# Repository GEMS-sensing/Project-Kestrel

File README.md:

<!--  -->

# Project-Kestrel
Core board for a Flight data logger, featuring interfaces to Talon boards ([SDI-12 Talon](https://github.com/GEMS-sensing/Talon-SDI12), [I2C Talon](https://github.com/GEMS-sensing/Talon-I2C), [Auxiliary Talon](https://github.com/GEMS-sensing/Talon-Auxiliary)) and external battery board ([Gonk](https://github.com/GEMS-sensing/Project-Gonk)). This is the core component of [Flight data logger](https://github.com/GEMS-sensing/DFM_-_Flight?tab=readme-ov-file).

# Repo Roadmap
#### [Documents](Documentation/) 

General document and image storage for repo and README

#### [Hardware](Hardware/)

Current board files (Eagle), Bill of Materials (BoM), and other design documents

#### [Production](Production/)

Contains the various Gerber and pick and place files required to have the Printed Circuit Boards (PCBs) manufactured or populated 

#### [Software](Software/)

The software associated with the piece of hardware, this is usually diagnostic software used for verifying or investigating the hardware

<!-- #### [Mechanical](Mechanical/)

Mechanical design files and assembly documents -->

<!-- #### [Testing](Testing/)

Scripts and results from the testing process and development process. Contains more detailed information about documented issues among other testing. 
 -->

## Overview
* **Type:** Logger
* **Interfaces:** Talon, Gonk
* **Release Version:** v1.9 - 2023/06/23

<!--  -->

## Features
### On-Board
* Modular interfaces for Talon daughterboards (x4)
	* Isolated I2C interface
	* Individual power control and monitoring
	* Firmware selectable GPIO/UART interface
	* Polarized connector
* Battery board interface 
	* I2C interface for battery power reporting
	* Polarized connector
* Multi-charger input
	* Solar panel (6V) input
	* High power (>2A) input for fast charge in no solar situations
* [Particle BSoM](https://docs.particle.io/b-series/) M.2 interface
	* Interface for the highly flexible Particle BSoM module
* Micro USB interface 
	* Programming and charging
* Power switch
	* Complete disconnect 
	* Tri position to allow for 'ON'-'TESTING'-'OFF' modes
* LED status indicators 
* Non-Contact safe mode circuit 
	* Safe mode circuit controlled by Hall effect sensor to allow for triggering with magnet from outside logger box
* Multi-rail power system
	* Allow for independent control of subsystems, on-board and off-board
* On-board GPS Module with battery backup for improved hot start
* SD Card interface
* On-board sensing for self diagnostics
	* Voltage/current sensing (8 positions)
	* Temperature
	* Humidity
	* Accelerometer, 3 axis
	* Magnatometer, 3 axis
	* Ambient light, multi channel
* Interchangeable SIM card (future support)
* RTC with rechargeable battery backup
* FRAM storage for low power backhaul batching
* Long period WatchDog control to prevent critical lockups 

<!-- ### Interface
* I<sup>2</sup>C
* M12 circular connector  -->

<!-- <picture>
  <source media="(prefers-color-scheme: dark)" srcset="Documents/Pinout_LIGHT.png">
  
</picture> -->

<!-- ## Specifications
* **Voltage - Supply:** 3.3V
* **Voltage - Logic:** 3.3V
* **Input Current (Avg, 1s period): 30.95&mu;A @ 3.3V**
* **Input Current (Avg, 5s period): 107.43&mu;A @ 3.3V**
* **Input Current (Max): 0.45mA @ 3.3V**

#### Sensor
**Temperature** [^1]
* Range: -40 ~ 125°C 
* Accuracy: &plusmn; 0.2°C
* Repeatability: &plusmn; 0.04°C

**Pressure** [^2]
* Range: 300 ~ 1200 hPa  
* Accuracy: &plusmn; 1 hPa
* Repeatability: &plusmn; 0.06 hPa

**Humidity** [^1]
* Range: 0 ~ 100%
* Accuracy: &plusmn; 2%
* Repeatability: 0.08%

[^1]: [SHT31 Datasheet](https://sensirion.com/media/documents/213E6A3B/63A5A569/Datasheet_SHT3x_DIS.pdf)
[^2]: [DPS368 Datasheet](https://www.infineon.com/dgdl/Infineon-DPS368-DS-v01_00-EN.pdf?fileId=5546d46269e1c019016a0c45105d4b40) -->

<!-- ## Version History

`v0.0` - Initial primal version with screw terminal

`v0.1` - Initial 'hard mount' version, using M12 connector

`v1.0` - Removed pullup select[^3], added logic level buffer and voltage reg on input

`v1.1` - Moved via away from connector pads to prevent bridging when soldering 

`v2.0` - Fixed issue with address select jumper[^3] -->

<!-- ## Jumper Settings 

> [!IMPORTANT]
> Jumper settings valid for version `v2.0` and beyond[^3]

[^3]: See Errata

**Configuration Jumpers**
| Jumper | Purpose | Open | Closed | Default | 
| ------ | ------- | ---------- | ---------- | ----- | 
| `JP1` | I<sup>2</sup>C Address Select | Base Address<sup>&dagger;</sup> | Alt Address<sup>&Dagger;</sup> | Open |

&dagger; SHT31 = `0x44`, DPS368 = `0x76`

&Dagger; SHT31 = `0x44`, DPS368 = `0x77`

 -->

## Version History

v1.7 updates:
- Connected DONE line on U26 to ensure consistent trip (prevent factory reset while using hall effect control)
- Changed label for 'STAT' led in upper right corner to 'SYS', this was done to reflect the current usage of the indicator and to eliminate confusion between this indicator and the indicator lamp for the battery charge (also labeled 'STAT')
- Switched amber LEDs to yellow

## Known Issues/Errata

#### Solder Jumper Stencil

**Version Affected:** All

**Issue:** Solar input does not support very low impedance sources (e.g. lead acid battery) - see details in issue [#20](https://github.com/GEMS-sensing/Project-Kestrel/issues/20)

**Workaround:** 

* Avoid use of low impedance batteries for input
* Include series impedance to prevent current spikes (not desirable)
* Perform board patch described in issue [#20](https://github.com/GEMS-sensing/Project-Kestrel/issues/20)

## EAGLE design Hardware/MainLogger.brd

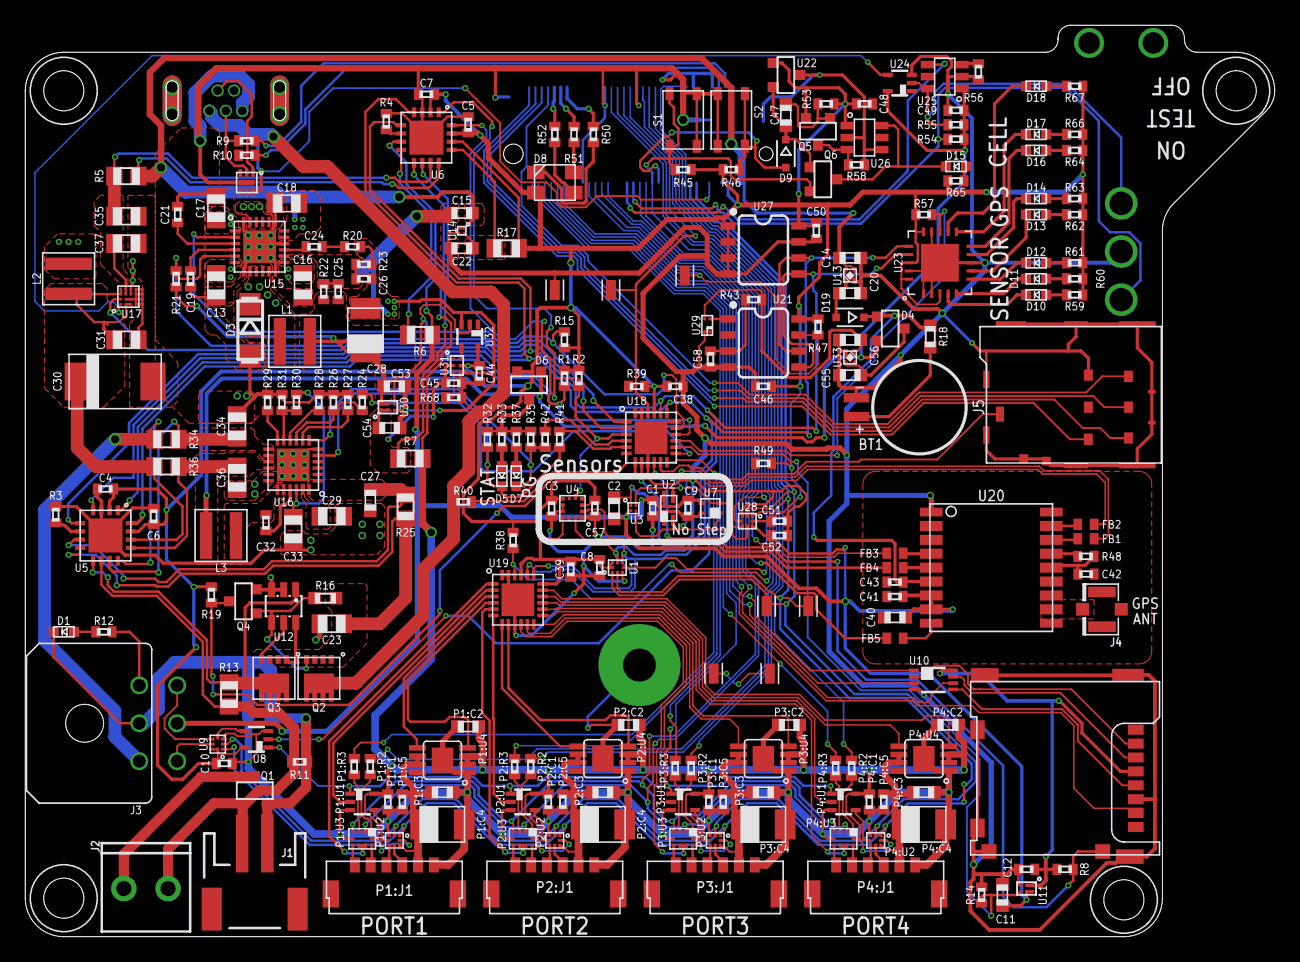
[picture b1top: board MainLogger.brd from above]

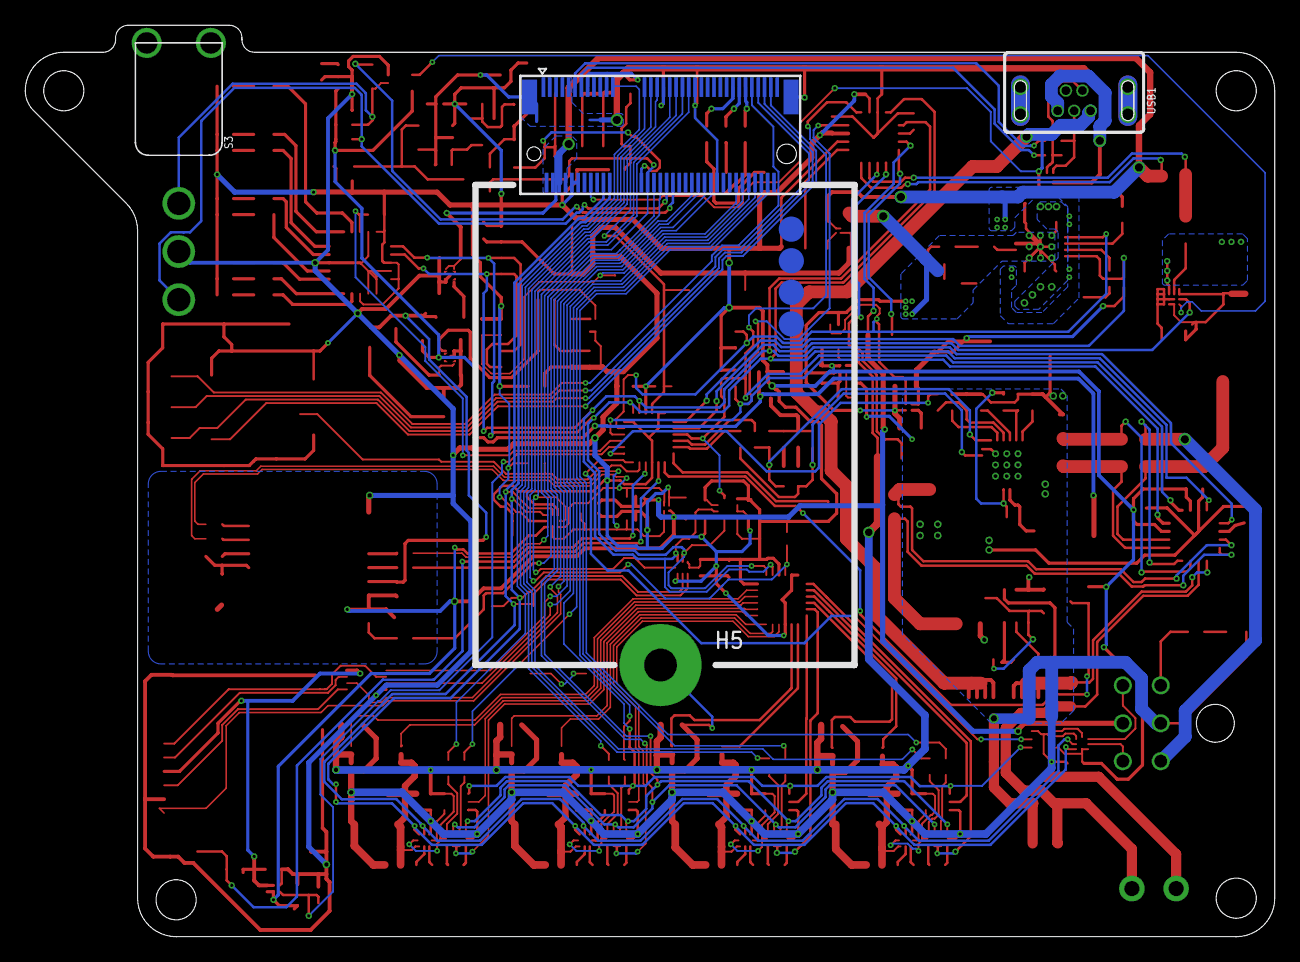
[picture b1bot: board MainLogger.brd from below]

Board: 2 copper layers, 98.9 x 72.1 mm, 262 parts (3 on the bottom side), 202 nets.

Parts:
$3_190_$_2021-12-10_02-09-55: B_SERIES_M.2EKEY_3042; PARTICLE_M.2EKEY
BT1: BATTERY_COINML621; ML621S
C1, C3, C4, C5, C6, C7, C8, C9, C10, C12, C38, C39, C41, C43, C44, C45, C46, C48, C49, C50, C51, C52, C57: 0.1uF; C0402
C2: 2.2uF; C0603
C11, C14, C15, C20, C22, C27, C40, C47, C53, C54, C55, C56: 1uF; C0603
C13, C16, C17, C18, C34: 22uF; C0805
C19: 1nF; C0402
C21, C25: 10nF; C0402
C23, C29, C35, C36, C37: 10uF; C0805
C24: 39pF; C0402
C26, C58: 100pF; C0402
C28: 100uF; C1411_TANT
C30: 220uF; C2917
C31: 1.5uF; C0805
C32: 47nF; C0402
C33: 4.7uF; C0805
C42: 47pF; C0402
D1, D12, D18: LEDRED0603; LED_0603
D2: RCLAMP3654; DFN_6_1.6X1.6
D3: CDBA3100; DO214AC
D4: BAT54C; SOT23-3
D5, D10, D13, D15, D16: LEDGREEN0603; LED_0603
D6: SOT23-3
D7, D11, D14, D17: LEDYELLOW0603; LED_0603
D8: CLVBA-FKA
D9, D19: BAT54WS; SOD323-R
FB1, FB2, FB3, FB4, FB5: R0402
H1, H2, H3, H4: 4_40
J1: JST-2-SMD
J2: SCREWTERMINAL-3.5MM-2_ROUND_RESTRICT
J3: GEMS_POWER_PLUGINPUT_RT; 2X3_MICROFIT_RT
J4: U.FL
J5: SIM_CDNANO_SF72; SIM_SF72
L1, L3: 1uH; WE-MAIA(4.1X4.1)
L2: 0.47uH; WE-MAPI(4.1X4.1)
P1:C1, P1:C5, P2:C1, P2:C5, P3:C1, P3:C5, P4:C1, P4:C5: 0.1uF; C0402
P1:C2, P2:C2, P3:C2, P4:C2: 2.2uF; C0603
P1:C3, P2:C3, P3:C3, P4:C3: 1uF; C0603
P1:C4, P2:C4, P3:C4, P4:C4: 100uF; C1411_TANT
P1:J1, P2:J1, P3:J1, P4:J1: CONN_TALON_LOGGER; 1X06_MICROLOCKPLUS_RT
P1:R2, P1:R3, P2:R2, P2:R3, P3:R2, P3:R3, P4:R2, P4:R3: 1k; R0402
P1:U1, P2:U1, P3:U1, P4:U1: SN74AUP1G08DCK; DCK_R-PDSO-G5
P1:U2, P2:U2, P3:U2, P4:U2: FXMAR2102UMLP; UQFN-8_1.4X1.2
P1:U3, P2:U3, P3:U3, P4:U3: FSA2258; MICROPAK_10
P1:U4, P2:U4, P3:U4, P4:U4: AP2411; MSOP_8EP
Q1, Q4: DMG3404; SOT23-3
Q2, Q3: MOSFET_PCH-DMP3036SFG; POWERDI3333-8
Q5, Q6: NX2301P; SOT23-3
R1, R2, R11, R19, R26, R32, R35, R40, R41, R42, R54, R55: 1M; R0402
R3, R20: 20k; R0402
R4: 2k; R0402
R5, R13, R25, R34, R36: 2m; R0805
R6, R7, R17: 10m; R0805
R8, R14, R15, R21, R30, R31, R38, R39, R47, R49, R53, R57: 100k; R0402
R9, R10: 27R; R0402
R12, R43: 1k; R0402
R16: 470k; R0603
R18: 750R; R0603
R22, R29, R33, R45, R46, R65: 10k; R0402
R23, R37: 2.7k; R0402
R24: 0R; R0402
R27, R28, R59, R60, R61, R62, R63, R64, R66, R67: 220R; R0402
R48: 10; R0402
R50, R51, R52, R68: 5.6k; R0402
R56: 130k; R0402
R58: 11k; R0402
S1, S2: BUTTON4.2X3.2; SWITCH_4.2X3.2
S3: SPDT7103K2CWAV2; 7103K2CWAV2
SD1: MICROSDMOLEX_503182; MICROSD_MOLEX_5031821852
TP1, TP2, TP5, TP6, TP7, TP8, TP9: TESTPOINT_DNP_RCU; TESTPOINT_0603
U1, U9, U28: FXMAR2102UMLP; UQFN-8_1.4X1.2
U2: VEML3328; VEML6075
U3: MMC5633; BGA_4
U4: BMA456; LGA-12_2X2
U5, U6: PAC1934QFN; QFN16
U7: SHT40; SHT4X
U8: SN74AUP1G08DCK; DCK_R-PDSO-G5
U10: SN74AUP3G34DCU; DCU_(R-PDSO-G8)
U11, U30: TCK111G; WCSP_6
U12: LTC4412S6; SOT23-6L
U13: TPS7A0331PDQ; X2SON
U14: LP59073.3VYKE; YKE0004
U15: MIC22602; QFN24_POWER
U16: BQ25616; QFN24_POWER
U17: TPS61282D; YFP0016
U18, U19: PCAL9535AQFN; QFN24
U20: MAX-M8W; MAX-M8
U21: MCP79412SOIC; SO08
U22: HALL_EFFECT_SI7201; SOT23-3
U23: PCA9634QFN; QFN20_5X5
U24: SN74LVC1G17DCK; DCK_R-PDSO-G5
U25, U26: TPL5010DDC; DDC_R-PDSO-G6
U27: MB85RC; SO08
U29: SIT1552; LD-4
U31: FPF2195BUCX; WCSP_6
U32: DCK_R-PDSO-G5
U33: TPS7A0218PDQ; X2SON
USB1: USB_MICROMUSB-K152; MUSB-K152-30

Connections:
3V3_AUX: C1.1, C2.1, C9.1, C11.1, C40.1, C41.1, C52.1, J3.5, R6.1, U2.4, U3.B1, U6.7, U7.3, U11.A2, U11.B2, U20.7, U20.8, U28.8
3V3_AUX_EN: R15.1, U15.2, U18.17, U30.C2, U32.2
3V3_AUX_PG: R21.1, U15.5, U18.1
3V3_BULK+: C25.1, C28.ANODE, C53.1, L1.P$2, R6.2, R21.2, R22.2, U6.8, U30.A2, U30.B2
3V3_CORE: $3_190_$_2021-12-10_02-09-55.10, $3_190_$_2021-12-10_02-09-55.12, C3.1, C4.1, C5.1, C6.1, C7.1, C8.1, C10.1, C38.1, C39.1, C44.1, C46.1, C48.1, C50.1, C51.1, C57.1, D6.2, D8.2, Q5.2, R1.2, R2.2, R15.2, R17.2, R19.2, R38.2, R39.2, R45.2, R46.2, R47.2, R49.2, R53.2, R57.2, R59.2, R60.2, R61.2, R62.2, R63.2, R64.2, R65.2, R66.2, R67.2, U1.1, U1.8, U4.3, U4.7, U4.10, U5.2, U5.15, U6.2, U6.14, U6.15, U8.5, U9.1, U9.8, U18.21, U19.18, U19.21, U21.8, U22.1, U23.3, U23.15, U23.18, U23.20, U26.1, U27.8, U28.1, U31.B2, U32.5
3V3_CORE+: C22.1, R17.1, U6.13, U14.A2
3V3_SD: C12.1, R8.2, SD1.4, U10.8, U11.A1, U11.B1
3V3_SD_EN: R14.2, U11.C2, U18.14
3V3_TALON: P1:C1.1, P1:C2.1, P1:U1.5, P1:U2.1, P1:U3.10, P1:U4.2, P1:U4.3, P2:C1.1, P2:C2.1, P2:U1.5, P2:U2.1, P2:U3.10, P2:U4.2, P2:U4.3, P3:C1.1, P3:C2.1, P3:U1.5, P3:U2.1, P3:U3.10, P3:U4.2, P3:U4.3, P4:C1.1, P4:C2.1, P4:U1.5, P4:U2.1, P4:U3.10, P4:U4.2, P4:U4.3, R7.2, U6.9
3V3_TALON+: C45.1, C54.1, R7.1, U6.10, U30.A1, U30.B1, U31.B1
!CE: R24.1, U18.13
!CHG_PG: D7.CATHODE, R35.1, R42.2, U16.7
!MODE: $3_190_$_2021-12-10_02-09-55.32, D9.A, R46.1, S2.1, S2.2
!RESET: $3_190_$_2021-12-10_02-09-55.34, FB5.2, Q6.2, R45.1, S1.1, S1.2
!TALON1_FAULT: P1:U4.5, U19.3
!TALON2_FAULT: P2:U4.5, U19.7
!TALON3_FAULT: P3:U4.5, U19.12
!TALON4_FAULT: P4:U4.5, U19.16
BAT: J3.1, R34.2, U5.12
BAT_CHG: C34.1, R34.1, U5.11, U16.13, U16.14
BCKP_GPS: C43.1, D4.1, D19.C, R18.1, U20.6
BCKP_GPS_REG: C20.1, D19.A, U13.1
BCKP_PRIME: C55.1, D4.3, U33.3, U33.4
BCKP_RTC: C58.1, R43.2, U21.3
BTST: C32.2, U16.21
CHG_SOURCE: Q4.3, R19.1, U18.7
CHG_STAT: D5.CATHODE, R32.1, R41.2, U16.5
CLK_OSC: U21.1, U29.2
COMP: C24.1, U15.15
CSA_EN: R1.1, U5.16, U6.16, U18.16
D+: $3_190_$_2021-12-10_02-09-55.11, R9.1
D+_IN: D2.2, R9.2, USB1.3
D-: $3_190_$_2021-12-10_02-09-55.13, R10.1
D-_IN: D2.1, R10.2, USB1.2
DELAY: C21.1, U15.3
EN_MAIN: U17.A1, U24.4
EN_MAIN_OD: R55.2, S3.1, U24.2, U25.6
FAULT_BUS: D1.ANODE, R12.2
FB: C25.2, C26.1, R22.1, R23.2, U15.14
GND: $3_190_$_2021-12-10_02-09-55.1, $3_190_$_2021-12-10_02-09-55.3, $3_190_$_2021-12-10_02-09-55.5, $3_190_$_2021-12-10_02-09-55.7, $3_190_$_2021-12-10_02-09-55.9, $3_190_$_2021-12-10_02-09-55.15, $3_190_$_2021-12-10_02-09-55.21, $3_190_$_2021-12-10_02-09-55.39, $3_190_$_2021-12-10_02-09-55.49, $3_190_$_2021-12-10_02-09-55.56, $3_190_$_2021-12-10_02-09-55.76, $3_190_$_2021-12-10_02-09-55.77, $3_190_$_2021-12-10_02-09-55.GND, BT1.-, C1.2, C2.2, C3.2, C4.2, C5.2, C6.2, C7.2, C8.2, C9.2, C10.2, C11.2, C12.2, C13.2, C14.2, C15.2, C16.2, C17.2, C18.2, C19.2, C20.2, C21.2, C22.2, C23.2, C26.2, C27.2, C28.CATHODE, C29.2, C30.-, C31.2, C33.2, C34.2, C35.2, C36.2, C37.2, C38.2, C39.2, C40.2, C41.2, C42.2, C43.2, C44.2, C45.2, C46.2, C48.2, C49.2, C50.2, C51.2, C52.2, C53.2, C54.2, C55.2, C56.2, C57.2, C58.2, D1.CATHODE, D2.EP, D3.A, J1.1, J3.2, J4.1, J4.2, J5.5, J5.CSW, J5.GND@1, J5.GND@2, J5.GND@3, J5.GND@4, J5.GND@5, J5.GND@6, J5.GND@7, J5.GND@8, J5.GND@9, J5.GND@10, P1:C1.2, P1:C2.2, P1:C3.2, P1:C4.CATHODE, P1:C5.2, P1:J1.1, P1:U1.3, P1:U2.4, P1:U3.5, P1:U4.1, P1:U4.EP, P2:C1.2, P2:C2.2, P2:C3.2, P2:C4.CATHODE, P2:C5.2, P2:J1.1, P2:U1.3, P2:U2.4, P2:U3.5, P2:U4.1, P2:U4.EP, P3:C1.2, P3:C2.2, P3:C3.2, P3:C4.CATHODE, P3:C5.2, P3:J1.1, P3:U1.3, P3:U2.4, P3:U3.5, P3:U4.1, P3:U4.EP, P4:C1.2, P4:C2.2, P4:C3.2, P4:C4.CATHODE, P4:C5.2, P4:J1.1, P4:U1.3, P4:U2.4, P4:U3.5, P4:U4.1, P4:U4.EP, Q1.2, Q4.2, R3.1, R4.1, R11.1, R14.1, R20.1, R23.1, R26.1, R27.1, R28.1, R29.2, R31.1, R56.1, R58.1, R68.1, S1.3, S1.4, S2.3, S2.4, S3.2, SD1.6, SD1.BODY@1, SD1.BODY@2, SD1.BODY@3, SD1.BODY@4, SD1.BODY@5, SD1.SW1, TP1.1, U1.4, U2.1, U3.A1, U4.1, U4.8, U4.9, U5.3, U5.EP, U6.3, U6.EP, U7.4, U8.3, U9.4, U10.4, U11.C1, U12.2, U12.3, U13.2, U13.EP, U14.B2, U15.7, U15.12, U15.16, U15.19, U15.24, U15.EP, U15.EP@1, U15.EP@2, U15.EP@3, U15.EP@4, U15.EP@5, U15.EP@6, U15.EP@7, U15.EP@8, U15.EP@9, U16.6, U16.17, U16.18, U16.EP, U16.EP@1, U16.EP@2, U16.EP@3, U16.EP@4, U16.EP@5, U16.EP@6, U16.EP@7, U16.EP@8, U16.EP@9, U17.B2, U17.C2, U17.D1, U17.D2, U17.D3, U17.D4, U18.9, U18.18, U18.23, U18.24, U18.EP, U19.9, U19.23, U19.24, U19.EP, U20.1, U20.10, U20.12, U21.4, U22.3, U23.1, U23.2, U23.8, U23.14, U23.19, U23.EP, U24.3, U25.2, U26.2, U26.4, U27.1, U27.2, U27.3, U27.4, U27.7, U28.4, U29.1, U29.4, U30.C1, U31.C2, U32.3, U33.2, U33.EP, USB1.5
GPS_ANT: J4.FEED, U20.11
GPS_INT: FB4.1, U18.8
GPS_INT_CLEAN: FB4.2, U20.5
I2C_EXT_EN: U8.2, U18.12
I2C_EXT_EN_OUT: U8.4, U9.5
I2C_GLOBAL_EN: $3_190_$_2021-12-10_02-09-55.64, P1:U1.1, P2:U1.1, P3:U1.1, P4:U1.1, U8.1
I2C_OB_EN: $3_190_$_2021-12-10_02-09-55.45, U1.5, U28.5
ICHG: R28.2, U16.10
ILIM: R27.2, U16.8
LED_BLUE: $3_190_$_2021-12-10_02-09-55.65, R52.2
LED_EN: R57.1, U18.15, U23.13
LED_GREEN: $3_190_$_2021-12-10_02-09-55.63, R51.2
LED_RED: $3_190_$_2021-12-10_02-09-55.61, R50.2
MISO: $3_190_$_2021-12-10_02-09-55.50, SD1.7
MOSI: $3_190_$_2021-12-10_02-09-55.52, U10.1
MOSI_BUF: SD1.3, U10.7
unnamed: R3.2, U5.6
unnamed: Q3.4, U12.5
unnamed: R41.1, U18.5
unnamed: BT1.+, R18.2
unnamed: R40.1, U18.6
unnamed: R42.1, U18.4
unnamed: R24.2, R26.2, U16.9
unnamed: C47.1, D9.C, Q6.1, U22.2
unnamed: D15.CATHODE, Q6.3, U26.6
unnamed: C47.2, Q5.1, R53.1
unnamed: D15.ANODE, R65.1
unnamed: R4.2, U6.6
unnamed: D7.ANODE, R37.1
unnamed: R68.2, U31.C1
unnamed: D5.ANODE, R33.1
unnamed: D8.3, R52.1
unnamed: D8.4, R51.1
unnamed: D8.1, R50.1
unnamed: FB5.1, U20.9
unnamed: J3.3, R12.1
unnamed: U31.A2, U32.4
unnamed: R56.2, U25.3
unnamed: Q5.3, R58.2, U26.3
unnamed: C24.2, R20.2
unnamed: D10.CATHODE, U23.4
unnamed: D11.CATHODE, U23.5
unnamed: D12.CATHODE, U23.6
unnamed: D13.CATHODE, U23.7
unnamed: D14.CATHODE, U23.9
unnamed: D16.CATHODE, U23.10
unnamed: D17.CATHODE, U23.11
unnamed: D18.CATHODE, U23.12
unnamed: D10.ANODE, R59.1
unnamed: D11.ANODE, R60.1
unnamed: D12.ANODE, R61.1
unnamed: D13.ANODE, R62.1
unnamed: D14.ANODE, R63.1
unnamed: D16.ANODE, R64.1
unnamed: D17.ANODE, R66.1
unnamed: D18.ANODE, R67.1
OB_INT: $3_190_$_2021-12-10_02-09-55.43, R39.1, TP7.1, U18.22
P1:3V3_TALON: P1:C3.1, P1:C4.ANODE, P1:C5.1, P1:J1.2, P1:U2.8, P1:U4.6, P1:U4.7
P1:I2C_EN_LOCAL: P1:U1.4, P1:U2.5
P1:N$1: P1:R2.1, P1:U3.1
P1:N$2: P1:R3.1, P1:U3.3
P1:RX_TALON: P1:J1.6, P1:U3.6
P1:SCL_EXT: P1:J1.4, P1:U2.6
P1:SDA_EXT: P1:J1.3, P1:U2.7
P1:TX_TALON: P1:J1.5, P1:U3.9
P2:3V3_TALON: P2:C3.1, P2:C4.ANODE, P2:C5.1, P2:J1.2, P2:U2.8, P2:U4.6, P2:U4.7
P2:I2C_EN_LOCAL: P2:U1.4, P2:U2.5
P2:N$1: P2:R2.1, P2:U3.1
P2:N$2: P2:R3.1, P2:U3.3
P2:RX_TALON: P2:J1.6, P2:U3.6
P2:SCL_EXT: P2:J1.4, P2:U2.6
P2:SDA_EXT: P2:J1.3, P2:U2.7
P2:TX_TALON: P2:J1.5, P2:U3.9
P3:3V3_TALON: P3:C3.1, P3:C4.ANODE, P3:C5.1, P3:J1.2, P3:U2.8, P3:U4.6, P3:U4.7
P3:I2C_EN_LOCAL: P3:U1.4, P3:U2.5
P3:N$1: P3:R2.1, P3:U3.1
P3:N$2: P3:R3.1, P3:U3.3
P3:RX_TALON: P3:J1.6, P3:U3.6
P3:SCL_EXT: P3:J1.4, P3:U2.6
P3:SDA_EXT: P3:J1.3, P3:U2.7
P3:TX_TALON: P3:J1.5, P3:U3.9
P4:3V3_TALON: P4:C3.1, P4:C4.ANODE, P4:C5.1, P4:J1.2, P4:U2.8, P4:U4.6, P4:U4.7
P4:I2C_EN_LOCAL: P4:U1.4, P4:U2.5
P4:N$1: P4:R2.1, P4:U3.1
P4:N$2: P4:R3.1, P4:U3.3
P4:RX_TALON: P4:J1.6, P4:U3.6
P4:SCL_EXT: P4:J1.4, P4:U2.6
P4:SDA_EXT: P4:J1.3, P4:U2.7
P4:TX_TALON: P4:J1.5, P4:U3.9
PMID: C29.1, U16.23
RC: C19.1, U15.4
REGN: C33.1, R30.2, U16.22
RTC_INT: $3_190_$_2021-12-10_02-09-55.62, R47.1, TP2.1, U21.7
RX: $3_190_$_2021-12-10_02-09-55.38, P1:U3.4, P2:U3.4, P3:U3.4, P4:U3.4, TP9.1
SCK: $3_190_$_2021-12-10_02-09-55.54, U10.3
SCK_BUF: SD1.5, U10.5
SCL: $3_190_$_2021-12-10_02-09-55.20, P1:U2.3, P2:U2.3, P3:U2.3, P4:U2.3, TP6.1, U1.2, U9.3, U28.3
SCL_AUX: FB2.1, U2.3, U3.A2, U7.2, U28.6
SCL_EXT: J3.6, U9.6
SCL_GPS: FB2.2, U20.17
SCL_OB: U1.7, U4.12, U5.4, U6.4, U18.19, U19.19, U21.6, U23.16, U27.6
SDA: $3_190_$_2021-12-10_02-09-55.22, P1:U2.2, P2:U2.2, P3:U2.2, P4:U2.2, TP5.1, U1.3, U9.2, U28.2
SDA_AUX: FB1.1, U2.2, U3.B2, U7.1, U28.7
SDA_EXT: J3.4, U9.7
SDA_GPS: FB1.2, U20.16
SDA_OB: U1.6, U4.2, U5.5, U6.5, U18.20, U19.20, U21.5, U23.17, U27.5
SD_CD: R8.1, SD1.SW2, U18.10
SD_CS: $3_190_$_2021-12-10_02-09-55.48, U10.6
SD_CS_BUF: SD1.2, U10.2
SENSOR_INT: R2.1, U4.5, U5.1, U6.1, U18.3
SIM_CD: J5.DSW, R49.1, U18.11
SIM_CLK: $3_190_$_2021-12-10_02-09-55.71, J5.3
SIM_DATA: $3_190_$_2021-12-10_02-09-55.73, J5.7
SIM_RST: $3_190_$_2021-12-10_02-09-55.69, J5.2
SIM_VCC: $3_190_$_2021-12-10_02-09-55.67, J5.1
SOLAR+: J1.2, J2.1, Q1.1, R11.2, R13.1, U5.10
SOLAR-: J2.2, Q1.3
STAT_CORE: D6.3, R32.2, R33.2, R35.2, R37.2
ST_CORE: Q2.4, Q4.1, R16.1, U12.4
SW: C32.1, L3.P$1, U16.19, U16.20
SW1: D3.C, L1.P$1, U15.8, U15.9, U15.10, U15.11, U15.20, U15.21, U15.22, U15.23
SW2: L2.P$2, U17.C3, U17.C4
SYS: C30.+, C31.1, L2.P$1, R36.2, U5.14, U17.A3, U17.A4, U17.B1, U17.C1
SYSCORE: C36.1, C49.1, D4.2, D6.1, L3.P$2, R36.1, R54.1, R55.1, U5.13, U16.15, U16.16, U24.5, U25.1
TALON1_EN: P1:U4.4, U19.4
TALON1_GPIOA: $3_190_$_2021-12-10_02-09-55.37, P1:R2.2
TALON1_GPIOB: $3_190_$_2021-12-10_02-09-55.72, P1:R3.2
TALON1_I2C_EN: P1:U1.2, U19.2
TALON1_SEL: P1:U3.7, P1:U3.8, U19.1
TALON2_EN: P2:U4.4, U19.8
TALON2_GPIOA: $3_190_$_2021-12-10_02-09-55.35, P2:R2.2
TALON2_GPIOB: $3_190_$_2021-12-10_02-09-55.70, P2:R3.2
TALON2_I2C_EN: P2:U1.2, U19.6
TALON2_SEL: P2:U3.7, P2:U3.8, U19.5
TALON3_EN: P3:U4.4, U19.13
TALON3_GPIOA: $3_190_$_2021-12-10_02-09-55.33, P3:R2.2
TALON3_GPIOB: $3_190_$_2021-12-10_02-09-55.68, P3:R3.2
TALON3_I2C_EN: P3:U1.2, U19.11
TALON3_SEL: P3:U3.7, P3:U3.8, U19.10
TALON4_EN: P4:U4.4, U19.17
TALON4_GPIOA: $3_190_$_2021-12-10_02-09-55.23, P4:R2.2
TALON4_GPIOB: $3_190_$_2021-12-10_02-09-55.66, P4:R3.2
TALON4_I2C_EN: P4:U1.2, U19.15
TALON4_SEL: P4:U3.7, P4:U3.8, U19.14
TALON_INT: $3_190_$_2021-12-10_02-09-55.41, R38.1, U19.22
TEST: $3_190_$_2021-12-10_02-09-55.40, R54.2, S3.3
TIMEPULSE: $3_190_$_2021-12-10_02-09-55.47, FB3.1
TIMEPULSE_CLEAN: FB3.2, U20.4
TS: R30.1, R31.2, U16.11
TX: $3_190_$_2021-12-10_02-09-55.36, P1:U3.2, P2:U3.2, P3:U3.2, P4:U3.2, TP8.1
VBULK: $3_190_$_2021-12-10_02-09-55.2, $3_190_$_2021-12-10_02-09-55.4, $3_190_$_2021-12-10_02-09-55.6, $3_190_$_2021-12-10_02-09-55.8, C13.1, C14.1, C15.1, C16.1, C17.1, C18.1, R5.1, U6.12, U13.3, U13.4, U14.A1, U14.B1, U15.1, U15.6, U15.13, U15.17, U15.18
VBULK+: C35.1, C37.1, R5.2, U6.11, U17.B3, U17.B4
VBULK_PG: U17.A2, U18.2
VBUS: C27.1, R25.2, U5.7, U16.1, U16.24
VCC_RF: C42.1, R48.1, U20.14
VDD_CLK: C56.1, R43.1, U29.3, U33.1
VPRIME: C23.1, Q2.1, Q2.2, Q2.3, Q3.1, Q3.2, Q3.3, R16.2, R25.1, U5.8, U12.6
VSET: R29.1, U16.12
VSOLAR: Q3.EP@1, Q3.EP@2, Q3.EP@3, Q3.EP@4, Q3.EP@5, R13.2, U5.9, U12.1
VUSB: $3_190_$_2021-12-10_02-09-55.16, D2.6, Q2.EP@1, Q2.EP@2, Q2.EP@3, Q2.EP@4, Q2.EP@5, R40.2, USB1.1
V_ANT: R48.2, U20.15
WDT_DONE: $3_190_$_2021-12-10_02-09-55.42, U25.4

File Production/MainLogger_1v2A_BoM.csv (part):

"Qty","Value","Device","Package","Parts","Description","DIGIKEY","DISP","MF","MPN","PROD_ID","SF_ID","VALUE","VALUE_PART",
"1","","CONN_02-JST-2MM-SMT","JST-2-SMD","J1","Genaric 2 terminal header","455-1749-1-ND","","JST","S2B-PH-SM4-TB(LF)(SN)","CONN-11443","","","",
"1","","CONN_023.5MM_ROUND_RESTRICT","SCREWTERMINAL-3.5MM-2_ROUND_RESTRICT","J2","Genaric 2 terminal header","ED2635-ND","","On Shore","OSTTE020161","","","","",
"1","","DIODE_CCBAT54CSOT23","SOT23-3","D6","Dual Diode, Common Cathode","BAT54CLT1GOSCT-ND","","ON Semiconductor","BAT54CLT1G","","","","",
"5","","FERRITE_BEAD1KS0402","R0402","FB1, FB2, FB3, FB4, FB5","Genaric Ferrite Bead","490-4003-1-ND","","Murata","BLM15HD102SN1D","","","","",
"4","","MOUNTING_HOLE4_NP","4_40","H1, H2, H3, H4","Genaric Mechanical Mounting Hole","DNP","","N/A","DNP","","","","",
"29","0.1uF","C-EU0.1UFC0402","C0402","C1, C4, C5, C6, C7, C8, C9, C10, C12, C14, C20, C38, C39, C41, C43, C46, C48, C49, C50, C51, C52, P1:C1, P1:C5, P2:C1, P2:C5, P3:C1, P3:C5, P4:C1, P4:C5","CAPACITOR, European symbol","490-4759-1-ND","","Murata","GCM155R71C104KA55D","","","","",
"1","0.47uH","INDUCTOR_MAPI_4.1X4.1","WE-MAPI(4.1X4.1)","L2","Genaric Inductor","732-744383560047HTCT-ND","","Wurth","744383560047HT","","","","",
"3","0R","R-EU_0.0R0402","R0402","R3, R4, R24","RESISTOR, European symbol","311-0.0JRCT-ND","","Yageo","RC0402JR-070RL","","","","0",
"1","1.5uF","C-EU1.5UFC0805","C0805","C31","CAPACITOR, European symbol","399-4930-1-ND","","Kemet","C0805C155K4RACTU","","","","",
"1","10","R-EU_10R0402","R0402","R48","RESISTOR, European symbol","A129603CT-ND","","TE","CRGCQ0402F10R","","","","10",
"15","100k","R-EU_100KR0402","R0402","P1:R1, P2:R1, P3:R1, P4:R1, R8, R14, R15, R21, R30, R31, R47, R49, R53, R56, R57","RESISTOR, European symbol","311-100KLRCT-ND","","Yageo","RC0402FR-07100KL","","","","100k",
"1","100pF","C-EU100PFC0402","C0402","C26","CAPACITOR, European symbol","311-1024-1-ND","","Yageo","CC0402JRNPO9BN101","","","","",
"5","100uF","CTANT_EU1411","C1411_TANT","C28, P1:C4, P2:C4, P3:C4, P4:C4","Genaric Tantalum Capacitor","478-5231-1-ND","","Kyocera AVX","TPSB107M010R0400","","","","",
"8","10k","R-EU_10KR0402","R0402","R22, R29, R33, R37, R45, R46, R58, R65","RESISTOR, European symbol","311-10.0KLRCT-ND","","Yageo","RC0402FR-0710KL","","","","10k",
"1","10k","R-EU_10KR0603","R0603","R39","RESISTOR, European symbol","311-10.0KHRCT-ND","","Yageo","RC0603FR-0710KL","","","","10k",
"3","10m","R-EU_0.01R0805","R0805","R17, R34, R36","RESISTOR, European symbol","CRF0805-FZ-R010ELFCT-ND","","Bourns","CRF0805-FZ-R010ELF","","","","",
"2","10nF","C-EU10NFC0402","C0402","C21, C25","CAPACITOR, European symbol","490-4762-1-ND","","Murata","GCM155R71H103KA55D","","","","",
"6","10uF","C-EU10UFC0805","C0805","C23, C29, C34, C35, C36, C37","CAPACITOR, European symbol","490-6473-1-ND","","Murata","GRM21BR61C106KE15K","","","","",
"1","130k","R-EU_130KR0603","R0603","R43","RESISTOR, European symbol","311-130KHRCT-ND","","Yageo","RC0603FR-07130KL","","","","130k",
"1","150k","R-EU_150KR0603","R0603","R38","RESISTOR, European symbol","311-150KHRCT-ND","","Yageo","RC0603FR-07150KL","","","","150k",
"12","1M","R-EU_1MR0402","R0402","R1, R2, R11, R19, R26, R32, R35, R40, R41, R42, R54, R55","RESISTOR, European symbol","311-1.00MLRCT-ND","","Yageo","RC0402FR-071ML","","","","1M",
"9","1k","R-EU_1KR0402","R0402","P1:R2, P1:R3, P2:R2, P2:R3, P3:R2, P3:R3, P4:R2, P4:R3, R12","RESISTOR, European symbol","311-1.00KLRCT-ND","","Yageo","RC0402FR-071KL","","","","1k",
"1","1k","R-EU_1KR0603","R0603","R18","RESISTOR, European symbol","311-1KLDCT-ND","","Yageo","AC0603FR-071KL","","","","1k",
"1","1nF","C-EU1NFC0402","C0402","C19","CAPACITOR, European symbol","490-3244-1-ND","","Murata","GRM1555C1H102JA01D","","","","",
"10","1uF","C-EU1UFC0603","C0603","C11, C15, C22, C27, C40, C47, P1:C3, P2:C3, P3:C3, P4:C3","CAPACITOR, European symbol","587-1251-1-ND","","Yaiyo Yuden","EMK107BJ105KA-T","","","","",
"2","1uH","INDUCTOR_MAIA_4.1X4.1","WE-MAIA(4.1X4.1)","L1, L3","Genaric Inductor","732-11737-1-ND","","Wurth","78438357010","","","","",
"6","2.2uF","C-EU2.2UFC0603","C0603","C2, C3, P1:C2, P2:C2, P3:C2, P4:C2","CAPACITOR, European symbol","1276-1183-1-ND","","Samsung","CL10A225KQ8NNNC","","","","",
"1","2.7k","R-EU_2.7KR0402","R0402","R23","RESISTOR, European symbol","CR0402-FX-2701GLFCT-ND","","Bourns","CR0402-FX-2701GLF","","","","2.7k",
"1","20k","R-EU_20KR0402","R0402","R20","RESISTOR, European symbol","CR0402-FX-2002GLFCT-ND","","Bourns","CR0402-FX-2002GLF","","","","20k",
"9","220R","R-EU_220R0402","R0402","R28, R59, R60, R61, R62, R63, R64, R66, R67","RESISTOR, European symbol","A129619CT-ND","","TE","CRGCQ0402F220R","","","","220",
"1","220uF","CTANT_EU2917","C2917","C30","Genaric Tantalum Capacitor","399-9744-1-ND","","Kemet","T491D227M010AT","","","","",
"4","22uF","C-EU22UFC0805","C0805","C13, C16, C17, C18","CAPACITOR, European symbol","490-9952-1-ND","","Murata","GRM219R61C226ME15L","","","","",
"2","27R","R-EU_27R0402","R0402","R9, R10","RESISTOR, European symbol","YAG3086CT-ND","","Yageo","RC0402FR-0727RL","","","","27",
"5","2m","R-EU_0.002R0805","R0805","R5, R6, R7, R13, R25","RESISTOR, European symbol","RHM.002AJCT-ND","","Rohm","PMR10EZPFV2L00","","","","",
"1","30k","R-EU_30KR0603","R0603","R44","RESISTOR, European symbol","311-30.0KHRCT-ND","","Yageo","RC0603FR-0730KL","","","","30k",
"1","39pF","C-EU39PFC0402","C0402","C24","CAPACITOR, European symbol","399-1018-1-ND","","Kemet","C0402C390J5GAC7867","","","","",
"3","4.7k","R-EU_4.7KR0603","R0603","R50, R51, R52","RESISTOR, European symbol","311-4.70KHRCT-ND","","Yageo","RC0603FR-074K7L","","","","4.7k",
"1","4.7uF","C-EU4.7UFC0805","C0805","C33","CAPACITOR, European symbol","399-7415-1-ND","","Kemet","C0805C475K4RACTU","","","","",
"1","470R","R-EU_470R0402","R0402","R27","RESISTOR, European symbol","311-470LRCT-ND","","Yageo","RC0402FR-07470RL","","","","470",
"1","470k","R-EU_470KR0603","R0603","R16","RESISTOR, European symbol","311-470KGRCT-ND","","Yageo","RC0603JR-07470KL","","","","470k",
"1","47nF","C-EU47PFC0402","C0402","C32","CAPACITOR, European symbol","490-3254-1-ND","","Murata","GRM155R71E473KA88D","","","","",
"1","47pF","C-EU47PFC0402","C0402","C42","CAPACITOR, European symbol","490-3254-1-ND","","Murata","GRM155R71E473KA88D","","","","",
"4","AP2411","AP2411","MSOP_8EP","P1:U4, P2:U4, P3:U4, P4:U4","AP24x1 - Current Limit Load Switch with Latch-Off","AP2411MP-13DICT-ND","AP2411","Diodes Inc","AP2411MP-13","","","","",
"1","BAT54C","DIODE_CCBAT54CSOT23","SOT23-3","D4","Dual Diode, Common Cathode","BAT54CLT1GOSCT-ND","","ON Semiconductor","BAT54CLT1G","","","","",
"1","BAT54WS","DIODE_SCHOTTKYSOD-323","SOD323-R","D9","Generic Shottky Diode","BAT54WS-TPCT-ND","","Micro Commercial","BAT54WS-TP","","","","",
"1","BATTERY_COINML621","BATTERY_COINML621","ML621S","BT1","Coin Cell Battery Holder","P044-ND","","Panasonic","ML-621S/DN","","","","",
"1","BQ25616","BQ25616","QFN24_POWER","U16","BQ25616 - Buck Battery Charger Standalone 1-Cell 3.0-A Buck Battery Charger with Power Path and 1.2-A","296-BQ25616RTWRCT-ND","","TI","BQ25616RTWR","","","","",
"2","BUTTON4.2X3.2","BUTTON4.2X3.2","SWITCH_4.2X3.2","S1, S2","Genaric SPST Push button","CKN10504CT-ND","","C&K","PTS810 SJG 250 SMTR LFS","","","","",
"1","B_SERIES_M.2EKEY_3042","B_SERIES_M.2EKEY_3042","PARTICLE_M.2EKEY","$3_190_$_2021-12-10_02-09-55","Particle B Series SoM","A115904CT-ND","","TE","2199230-4","","","","",
"1","CDBA3100","DIODE_SCHOTTKYDO-214AC","DO214AC","D3","Generic Shottky Diode","641-1747-1-ND","","Comchip","CDBA3100-HF","","","","",
"1","CLVBA-FKA","CLVBA-FKA","CLVBA-FKA","D8","Cree RGB LED, Small Package, Common Anode, CLVBA-FKA","CLVBA-FKA-CAEDH8BBB7A363CT-ND","","Cree","CLVBA-FKA-CAEDH8BBB7A363","","","","",
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
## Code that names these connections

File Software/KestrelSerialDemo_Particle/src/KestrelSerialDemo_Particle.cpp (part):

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
// #define NUM_MCP2301x_ICs   1

// const uint8_t I2C_GLOBAL_EN = 0; //FIX!

void setup();
void loop();
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	constexpr uint16_t WD_HOLD  = D2;
	// constexpr uint16_t EXT_EN   = 13;
	// constexpr uint16_t SD_EN    = 1;
	constexpr uint16_t SD_CS    = D8;
	// constexpr uint16_t SD_CD    = 18;
	// constexpr uint16_t SDA_CTRL = 5;
	// constexpr uint16_t TIP      = 18;
	// constexpr uint16_t GPIOXA 	= 17;
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	// constexpr uint16_t Port1A 	= A2;
	// constexpr uint16_t Port2A 	= A1;
	// constexpr uint16_t Port3A 	= A0;
	constexpr uint16_t TALON1_GPIOA = A3;
	constexpr uint16_t TALON1_GPIOB = D7;
	constexpr uint16_t TALON2_GPIOA = A2;
	constexpr uint16_t TALON2_GPIOB = D6;
	constexpr uint16_t TALON3_GPIOA = A1;
	constexpr uint16_t TALON3_GPIOB = D5;
	constexpr uint16_t I2C_GLOBAL_EN = D23; //FIX!
	constexpr uint16_t I2C_OB_EN = A6; //FIX!
}

namespace PinsIO { //For Kestrel v1.1
	constexpr uint16_t VUSB = 5;
}

namespace PinsIOAlpha {
	constexpr uint16_t I2C_EXT_EN = 10;
	constexpr uint16_t SD_CD = 8;
	constexpr uint16_t SD_EN = 12;
	constexpr uint16_t AUX_EN = 15;
	constexpr uint16_t CE = 11;
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	// digitalWrite(Pins::SD_EN, HIGH); //Set enable pin to turn on power
	I2C_GlobalEn(false);
	I2C_OnBoardEn(true);
	ioAlpha.pinMode(PinsIOAlpha::SD_CD, INPUT);
	ioAlpha.pinMode(PinsIOAlpha::SD_EN, OUTPUT);
	ioAlpha.setIntConfig(true, false, true, false); //Setup ganged inerrupts with push pull output, active high, cleared by reading GPIO regs 
	ioAlpha.digitalWrite(PinsIOAlpha::SD_EN, HIGH); //Turn on 3v3 to SD
	ioAlpha.setIntPinConfig(PinsIOAlpha::SD_CD, false, LOW); //Interrupt if SD_CD goes HIGH
	ioAlpha.setInterrupt(PinsIOAlpha::SD_CD, true); //turn on interrupt for OVF1 pin
	ioAlpha.clearInterrupt(BOTH); //Clean both interrupts 

	boolean SDError = false;
	pinMode(Pins::SD_CS, OUTPUT);
	// SPI.beginTransaction(SPISettings(4000000, MSBFIRST, SPI_MODE0));
	SPI.beginTransaction(SPISettings(20000000, MSBFIRST, SPI_MODE0)); //Test max speed mode
	// SPI.setDataMode(SPI_MODE0);
	// SPI.setClockDivider(SPI_CLOCK_DIV2); //Sts SPI clock to 4 MHz for an 8 MHz system clock
	if(ioAlpha.digitalRead(PinsIOAlpha::SD_CD)) {
		Serial.println("\tERROR: SD Not Inserted");
		return SDError;
	}

	if(!SD_Init) {
		if (!SD.begin(Pins::SD_CS)) {
			Serial.println("\tERROR: Init Failed");
			SDError = true; 
			return SDError;
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{
	I2C_GlobalEn(false);
	I2C_OnBoardEn(true);
	ioAlpha.pinMode(PinsIOAlpha::SD_CD, INPUT);
	ioAlpha.pinMode(PinsIOAlpha::SD_EN, OUTPUT);

	ioAlpha.digitalWrite(PinsIOAlpha::SD_EN, HIGH); //Turn on 3v3 to SD

	boolean SDError = false;
	pinMode(Pins::SD_CS, OUTPUT);
	SPI.beginTransaction(SPISettings(4000000, MSBFIRST, SPI_MODE0));
	// SPI.beginTransaction(SPISettings(20000000, MSBFIRST, SPI_MODE0)); //Test max speed mode
	// SPI.setDataMode(SPI_MODE0);
	// SPI.setClockDivider(SPI_CLOCK_DIV2); //Sts SPI clock to 4 MHz for an 8 MHz system clock
	if(ioAlpha.digitalRead(PinsIOAlpha::SD_CD)) {
		Serial.println("\tERROR: SD Not Inserted");
		return SDError;
	}

	if(!SD_Init) {
		if (!SD.begin(Pins::SD_CS)) {
			Serial.println("\tERROR: Init Failed");
			SDError = true; 
			return SDError;
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	I2C_GlobalEn(false);
	I2C_OnBoardEn(true);
	//Turn on external I2C port
	ioAlpha.pinMode(PinsIOAlpha::I2C_EXT_EN, OUTPUT);
	ioAlpha.digitalWrite(PinsIOAlpha::I2C_EXT_EN, HIGH);

	I2C_GlobalEn(true);
	I2C_OnBoardEn(false);
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	// Serial.println(digitalRead(BGPWR));
	I2C_GlobalEn(false);
  	I2C_OnBoardEn(true);
	ioAlpha.pinMode(PinsIO::VUSB, INPUT); //Set to input to sense 
	uint8_t State = ioAlpha.digitalRead(PinsIO::VUSB); //Read state of port
	Serial.print("\tUSB Status: ");
	Serial.println(State);
}
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
	I2C_OnBoardEn(false);
	I2C_GlobalEn(true);
	// pinMode(Pins::TALON2_GPIOB, OUTPUT);
	// digitalWrite(Pins::TALON2_GPIOB, HIGH); //Connect to internal I2C
	pinMode(Pins::TALON2_GPIOB, OUTPUT);
	digitalWrite(Pins::TALON2_GPIOB, HIGH); //Connect to internal I2C
	Serial.println(ioTalonI2C.begin());

	ioTalonI2C.pinMode(POS_DETECT, INPUT); //Set position detect as normal pullup (has external pullup)
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	// ioTalonI2C.digitalWrite(0, HIGH); //Toggle port 1 on
	// ioTalonI2C.digitalWrite(4, HIGH); //Make sure signal is turned on

	// digitalWrite(Pins::TALON1_GPIOB, LOW); //Connect to external I2C
	// digitalWrite(Pins::TALON2_GPIOB, LOW); //Connect to external I2C

	// SWITCHED READING TEST - BEGIN /////////////////////////////////////////////////////////////////////////////////////////////////
	// ioTalonI2C.digitalWrite(SENSE_EN, LOW); //Default sense to off
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	// 	ioTalonI2C.digitalWrite(i + 4, HIGH); //Turn on all enable
	// 	ioTalonI2C.digitalWrite(i, LOW); //Turn off all power
	// }
	// digitalWrite(Pins::TALON2_GPIOB, LOW); //Connect to external I2C
	// for(int i = 0; i < 4; i++) {
	// 	digitalWrite(Pins::TALON2_GPIOB, HIGH); //Connect to internal I2C
	// 	// ioTalonI2C.digitalWrite(i + 4, HIGH); //Turn on specific data channel
	// 	ioTalonI2C.digitalWrite(i, HIGH); //Turn on specific power channel
	// 	digitalWrite(Pins::TALON2_GPIOB, LOW); //Connect to external I2C
	// 	uint8_t error_dps368 = 0; //DEBUG! FIX! Change library to return stuff properly
	// 	pressureSense.begin(Wire); //Initialize DPS368 sensor //DEBUG! FIX! Change library to return stuff properly
	// 	uint8_t error_sht31 = rhSense.begin(0x44); //Initialize SHT31 sensor
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	// 	Serial.print("Temp (DPS368): "); Serial.print(temp_dps368, 2); Serial.print(" °C\t"); //Print temp to 2 decimal places
	// 	Serial.print("Pressure: "); Serial.print(pressure, 2); Serial.print(" mBar\t"); //Print pressure to 2 decimal places
	// 	Serial.print("Humidity: "); Serial.print(humidity, 2); Serial.print(" %\n"); //Print humidity to 2 decimal places
	// 	digitalWrite(Pins::TALON2_GPIOB, HIGH); //Connect to internal I2C
	// 	// ioTalonI2C.digitalWrite(i + 4, LOW); //Turn off specific data channel
	// 	ioTalonI2C.digitalWrite(i, LOW); //Turn off specific power channel
	// 	digitalWrite(Pins::TALON2_GPIOB, LOW); //Connect to external I2C
	// }
	// SWITCHED READING TEST - END /////////////////////////////////////////////////////////////////////////////////////////////////

	// BUS READING TEST - BEGIN /////////////////////////////////////////////////////////////////////////////////////////////////
	// ioTalonI2C.digitalWrite(4, LOW); //Disable port 0 data //DEBUG!
	// ioTalonI2C.digitalWrite(0, LOW); //Disable port 0 power //DEBUG!
	digitalWrite(Pins::TALON2_GPIOB, LOW); //Connect to external I2C
	uint8_t error_dps368A = 0; //DEBUG! FIX! Change library to return stuff properly
	pressureSenseA.begin(Wire, 0x76); //Initialize DPS368 sensor //DEBUG! FIX! Change library to return stuff properly
	uint8_t error_sht31A = rhSenseA.begin(0x44); //Initialize SHT31 sensor
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
	// BUS READING TEST - END /////////////////////////////////////////////////////////////////////////////////////////////////
	// LOOPBACK TEST - BEGIN ///////////////////////////////////////////////////
	digitalWrite(Pins::TALON2_GPIOB, HIGH); //Connect to internal I2C
	ioTalonI2C.pinMode(15, OUTPUT); //Set Loopback control as output
	ioTalonI2C.digitalWrite(15, LOW); //Disable loopback output
	digitalWrite(Pins::TALON2_GPIOB, LOW); //Turn off I2C OB
	Serial.println("LOOPBACK TEST:");
	Wire.beginTransmission(0x30); //Request ACK from EEPROM
	Wire.write(0x00);
	int Error = Wire.endTransmission(); 
	Serial.print("\tExt - Loopback Disabled: ");
	Serial.println(Error);
	digitalWrite(Pins::TALON2_GPIOB, HIGH); //Connect to internal I2C
	ioTalonI2C.digitalWrite(15, HIGH); //Enable loopback output
	digitalWrite(Pins::TALON2_GPIOB, LOW); //Turn off I2C OB
	Wire.beginTransmission(0x30); //Request ACK from EEPROM
	Wire.write(0x00);
	Error = Wire.endTransmission(); 
	Serial.print("\tExt - Loopback Enabled: ");
	Serial.println(Error);
	digitalWrite(Pins::TALON2_GPIOB, HIGH); //Connect to internal I2C
	ioTalonI2C.digitalWrite(15, HIGH); //Enable loopback output
	Wire.beginTransmission(0x30); //Request ACK from EEPROM
	Wire.write(0x00);
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	Serial.print("\tOB - Loopback Enabled: ");
	Serial.println(Error);
	ioTalonI2C.digitalWrite(15, LOW); //Disable loopback output
	// digitalWrite(Pins::TALON2_GPIOB, LOW); //Turn off I2C OB
	Wire.beginTransmission(0x30); //Request ACK from EEPROM
	Wire.write(0x00);
	Error = Wire.endTransmission(); 
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{
	Serial1.begin(115200); //High speed serial test
	Serial1.println("DEADBEEF");
	// pinMode(Pins::TALON1_GPIOB, OUTPUT);
	// analogWrite(Pins::TALON1_GPIOB, 128);
}

void SendBreak()
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
void I2C_GlobalEn(bool State)
{
	pinMode(Pins::I2C_GLOBAL_EN, OUTPUT);
	digitalWrite(Pins::I2C_GLOBAL_EN, State);
}

void I2C_OnBoardEn(bool State)
{
	pinMode(Pins::I2C_OB_EN, OUTPUT);
	digitalWrite(Pins::I2C_OB_EN, State);
}

void SetDefaultPins()
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
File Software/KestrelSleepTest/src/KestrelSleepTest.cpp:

/******************************************************/
//       THIS IS A GENERATED FILE - DO NOT EDIT       //
/******************************************************/

#include "Particle.h"
#line 1 "c:/Users/schul/Documents/Project-Kestrel/Software/KestrelSleepTest/src/KestrelSleepTest.ino"
/*
 * Project KestrelSleepTest
 * Description:
 * Author:
 * Date:
 */

#include <MCP23018.h>
#include "SparkFun_Ublox_Arduino_Library.h"

void setup();
void loop();
#line 11 "c:/Users/schul/Documents/Project-Kestrel/Software/KestrelSleepTest/src/KestrelSleepTest.ino"
SFE_UBLOX_GPS myGPS;
MCP23018 ioAlpha(0x20);

const uint8_t RTC_INT = D22; //FIX!
const uint8_t CSA_EN = 14; //FIX!
const uint8_t LED_EN = 13; //FIX!
const uint8_t AUX_EN = 15; //FIX!
// const uint8_t I2C_OB_EN = A6; //FIX!

const uint8_t FRAM_ADR = 0x50; 
const uint8_t ACCEL_ADR = 0x15;

const uint8_t I2C_OB_EN = D21;
const uint8_t I2C_GLOBAL_EN = D23;

SYSTEM_MODE(AUTOMATIC);

void setup() {
  pinMode(I2C_OB_EN, OUTPUT);
  digitalWrite(I2C_OB_EN, HIGH);
  Wire.begin();
  
  ioAlpha.begin();
  ioAlpha.pinMode(12, OUTPUT); //LOW
  ioAlpha.pinMode(11, OUTPUT); //LOW
  ioAlpha.pinMode(10, OUTPUT); //LOW
  ioAlpha.pinMode(9, INPUT); 
  ioAlpha.pinMode(8, INPUT);
  ioAlpha.pinMode(7, INPUT);
  ioAlpha.pinMode(6, INPUT);
  ioAlpha.pinMode(5, INPUT);
  ioAlpha.pinMode(4, INPUT);
  ioAlpha.pinMode(3, INPUT);
  ioAlpha.pinMode(2, INPUT); //DEBUG! Return to INPUT_PULLUP
  ioAlpha.pinMode(1, INPUT);
  ioAlpha.pinMode(0, INPUT);

  ioAlpha.pinMode(CSA_EN, OUTPUT);
  ioAlpha.pinMode(LED_EN, OUTPUT);
  ioAlpha.pinMode(AUX_EN, OUTPUT);
  ioAlpha.digitalWrite(AUX_EN, HIGH); //DEBUG!
  myGPS.begin();

  pinMode(A4, INPUT);
  pinMode(A5, INPUT);

  // pinMode(I2C_OB_EN, OUTPUT);
  // digitalWrite(I2C_OB_EN, HIGH); //Enable onboard communication 
}

void loop() {
  // //Shutdown Accel
	Wire.beginTransmission(ACCEL_ADR);
	Wire.write(0x0D); //Write to control register
	Wire.write(0x01); //Set power down
	Wire.endTransmission();

  //Shutdown FRAM
	Wire.beginTransmission(0xA0);
	Wire.write((FRAM_ADR << 1) | 0x01); //Shift to add "r/w" bit //FIX!
	Wire.endTransmission(false);
	Wire.beginTransmission(0x43);
	Wire.endTransmission();

  Wire.beginTransmission(0x20);
  Wire.write(0x0A);
  Wire.write(0b01000000); //Set INT pins to be ORed and driven
  Wire.endTransmission();

  Wire.beginTransmission(0x21);
  Wire.write(0x0A);
  Wire.write(0b01000000); //Set INT pins to be ORed and driven
  Wire.endTransmission();

  ioAlpha.digitalWrite(CSA_EN, LOW); //Turn off CSAs
  ioAlpha.digitalWrite(LED_EN, HIGH); //Turn off LEDs for ultra low power
  ioAlpha.digitalWrite(AUX_EN, LOW); //Turn off auxiliary power
  // ioAlpha.digitalWrite(AUX_EN, HIGH); //DEBUG!
  // myGPS.powerOff(60000);

  digitalWrite(I2C_OB_EN, LOW);

  // SystemSleepConfiguration config;
	// 	config.mode(SystemSleepMode::ULTRA_LOW_POWER)
	// 	.gpio(RTC_INT, FALLING);

  SystemSleepConfiguration config;
		config.mode(SystemSleepMode::ULTRA_LOW_POWER)
		.gpio(RTC_INT, FALLING);
    // .gpio(A4, RISING)
    // .gpio(A5, RISING);
		SystemSleepResult result = System.sleep(config);
}

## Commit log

2021-10-01 Continued schematic capture
    Schematic capture and added modules for Talon interface
2021-10-01 Added VELM3328
2021-10-05 Continued layout and schematic updates
2021-10-06 Initial copper layout complete, cleanup and silk required
2021-10-08 Layout and cleanup complete, review required
    Also add test points
2021-10-12 Layout, gerbers, and BoM for v0.0 - sent to fab
2021-11-23 Added production files for v0.1, v0.2
2021-11-23 v1.0 Update
    Many fixes, see ECO and Github issues documentation, v1.0 sent to fab
2021-12-09 Added v1.0 BoM
2021-12-09 Updated gitignore for C++/Particle files
2021-12-10 v1.1 Update
    Added SIM card, updated pinouts, fixed switch circuit
2021-12-22 Updated address note and added renumber file
2021-12-22 v1.2 Updates
    Added I2C_AUX buffer, switched SHT31 to SHT41
2021-12-22 Added series resistors for GPIO output
2021-12-22 v1.2 Gerbers generated
2021-12-22 Switched RTC crystal to TCXO
2022-01-05 Added measures, fixed value of R49
2022-01-12 Fixed passive value, added BoM
2022-01-12 Added SleepTest software
    Added sleep test program to test the low power sleep level of the device
2022-01-24 Added submodules for serial demo
2022-01-24 Updated MCP7940 lib
2022-01-24 Added particle serial demo
2022-01-25 Removed submodule Software/KestrelSerialDemo_Particle/lib/Adafruit_BusIO
2022-01-27 Added non-particle serial demo
2022-01-27 Updated sleep test to include GPS shutdown
2022-01-27 Updated serial demo to support additional testing
2022-01-27 v1.3 Updates
    Reconfigured backup battery charger
2022-02-18 Updated modules for serial interface
2022-02-18 Updated serial demo
2022-03-02 Updated submodule Software/KestrelSerialDemo_Particle/lib/PAC1932_Library
2022-03-02 Added CSA channel toggle in serial demo
2022-03-02 Added immediate initialization of WDT
2022-03-09 Updated v1.4 for production
2022-03-09 Updated C42 part val
    Fixed C42 part value to correctly reflect 47pF value
2022-03-09 Updated part value for C32
    Made C32 reflect the correct library part
2022-03-30 Added license
2022-04-25 v1.5 Update
    Updated schematic and layout, boards sent to fab
2022-04-25 Added loopback testing and memory testing to SerialDemo_Particle
2022-05-17 Added v1.5 production outputs
2022-06-14 v1.6 Update
2022-06-14 Update sleep test script
2022-06-14 Updated submodule Software/KestrelSerialDemo_Particle/lib/Adafruit_ADS1X15
2022-06-14 Added submodule Software/KestrelSerialDemo_Particle/lib/PACL9535A_Library
2022-06-14 Updated submodule Software/KestrelSerialDemo_Particle/lib/PACL9535A_Library
2022-08-10 Updated libraries for testing code
2022-12-20 Updated CSV for DNPs
2022-12-20 Added fix for WDT
2023-05-15 Generated production files for v1.7
2023-05-15 v1.8 Updates
    - Changed accel (#1)
    - Fixed backup regulator issue (#16)
    - Fixed TCXO overvoltage issue (#19)
2023-06-16 v1.9 updates
    Added series diode in gps/rtc bat charger to prevent reverse current
2023-06-16 Added production files for v1.9
2023-06-16 Fixed soldermask error
    Fixed error in soldermask on X2SOM packages
2023-06-23 Fixed silkscreen numbering
2023-06-29 Updated `R3` Value
    Changed `R3` to 20k to deal with address conflict
2024-09-01 Updated readme and images
2024-09-01 Fixed issue links
2024-11-02 Added documentation on versions
2024-11-02 Added support for BMA456 in serial demo

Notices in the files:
parts and their libraries:
SparkFun-Connectors: Licensing: Creative Commons ShareAlike 4.0 International - https://creativecommons.org/licenses/by-sa/4.0
Particle-Devices: Licensing: Designed by Particle.
